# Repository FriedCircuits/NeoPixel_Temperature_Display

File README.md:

NeoPixel Temperature Ring
================

Readme place holder

More info on

http://mobilewill.us

http://www.mobilewill.us/2015/07/arduino-zero-has-arrived.html

License: All source code and designs are released under 

Creative Commons 

CC BY-SA

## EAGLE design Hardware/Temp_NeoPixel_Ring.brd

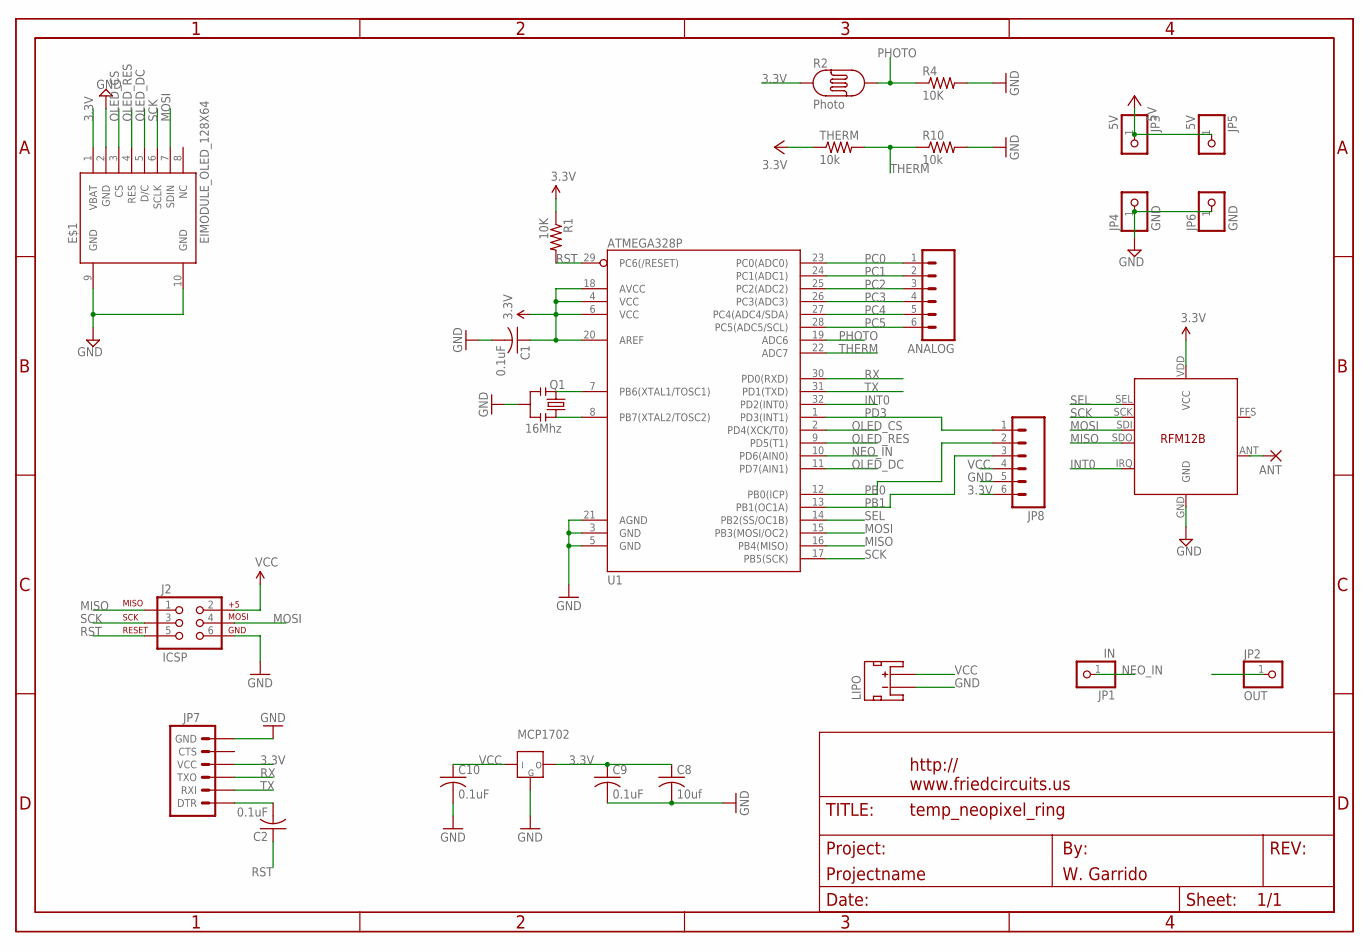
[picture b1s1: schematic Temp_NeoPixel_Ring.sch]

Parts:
ANALOG: M06LOCK; 1X06_LOCK
ANT: 1,6/0,8
C1, C2, C9, C10: 0.1uF; C0805K
C8: 10uf; C0805K
E$1: EIMODULE_OLED_128X64
J2: ICSP; 2X3_LOCK
JP1: IN; 1X01-CLEANBIG
JP2: OUT; 1X01-CLEANBIG
JP3, JP5: 5V; 1X01-CLEANBIG
JP4, JP6: GND; 1X01-CLEANBIG
JP7: ARDUINO_SERIAL_PROGRAMLOCK; 1X06_LOCK
JP8: M06LOCK; 1X06_LOCK
LIPO: LIPO-3.7-6V; JST-2-SMD
MCP1702: MCP1702SOT89; SOT89-3
Q1: 16Mhz; RESONATOR-SMD
R1, R4: 10K; R0805
R2: Photo; PHOTOCELL
R10: 10k; R0805
THERM: 10k; R0805
U1: ATMEGA328P; TQFP32-08
U$1: FRAME_DINA4_L; FC_CREDIT
U$2: RFM12B

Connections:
3.3V: C1.1, C8.1, C9.1, E$1.1 (VBAT), J2.2, JP7.4 (VCC), JP8.6, MCP1702.3 (E), R1.1, R2.1, THERM.1, U1.4 (VCC), U1.6 (VCC), U1.18 (AVCC), U1.20 (AREF), U$2.VDD (VCC)
GND: C1.2, C8.2, C9.2, C10.2, E$1.2 (GND), E$1.9 (GND), E$1.10 (GND), J2.6, JP4.1, JP6.1, JP7.6 (GND), JP8.5, LIPO.1 (-), MCP1702.1 (B), Q1.2, R4.2, R10.2, U1.3 (GND), U1.5 (GND), U1.21 (AGND), U$2.GND
INT0: U1.32 (PD2(INT0)), U$2.IRQ
MISO: J2.1, U1.16 (PB4(MISO)), U$2.SDO
MOSI: E$1.7 (SDIN), J2.4, U1.15 (PB3(MOSI/OC2)), U$2.SDI
unnamed: C2.2, JP7.1 (DTR)
unnamed: Q1.1, U1.8 (PB7(XTAL2/TOSC2))
unnamed: Q1.3, U1.7 (PB6(XTAL1/TOSC1))
unnamed: ANT.1, U$2.ANT
NEO_IN: JP1.1, U1.10 (PD6(AIN0))
OLED_CS: E$1.3 (CS), U1.2 (PD4(XCK/T0))
OLED_DC: E$1.5 (D/C), U1.11 (PD7(AIN1))
OLED_RES: E$1.4 (RES), U1.9 (PD5(T1))
OUT: JP2.1
PB0: JP8.2, U1.12 (PB0(ICP))
PB1: JP8.3, U1.13 (PB1(OC1A))
PC0: ANALOG.1, U1.23 (PC0(ADC0))
PC1: ANALOG.2, U1.24 (PC1(ADC1))
PC2: ANALOG.3, U1.25 (PC2(ADC2))
PC3: ANALOG.4, U1.26 (PC3(ADC3))
PC4: ANALOG.5, U1.27 (PC4(ADC4/SDA))
PC5: ANALOG.6, U1.28 (PC5(ADC5/SCL))
PD3: JP8.1, U1.1 (PD3(INT1))
PHOTO: R2.2, R4.1, U1.19 (ADC6)
RST: C2.1, J2.5, R1.2, U1.29 (PC6(/RESET))
RX: JP7.3 (TXO), U1.30 (PD0(RXD))
SCK: E$1.6 (SCLK), J2.3, U1.17 (PB5(SCK)), U$2.SCK
SEL: U1.14 (PB2(SS/OC1B)), U$2.SEL
THERM: R10.1, THERM.2, U1.22 (ADC7)
TX: JP7.2 (RXI), U1.31 (PD1(TXD))
VCC: C10.1, JP3.1, JP5.1, JP8.4, LIPO.2 (+), MCP1702.2 (C)

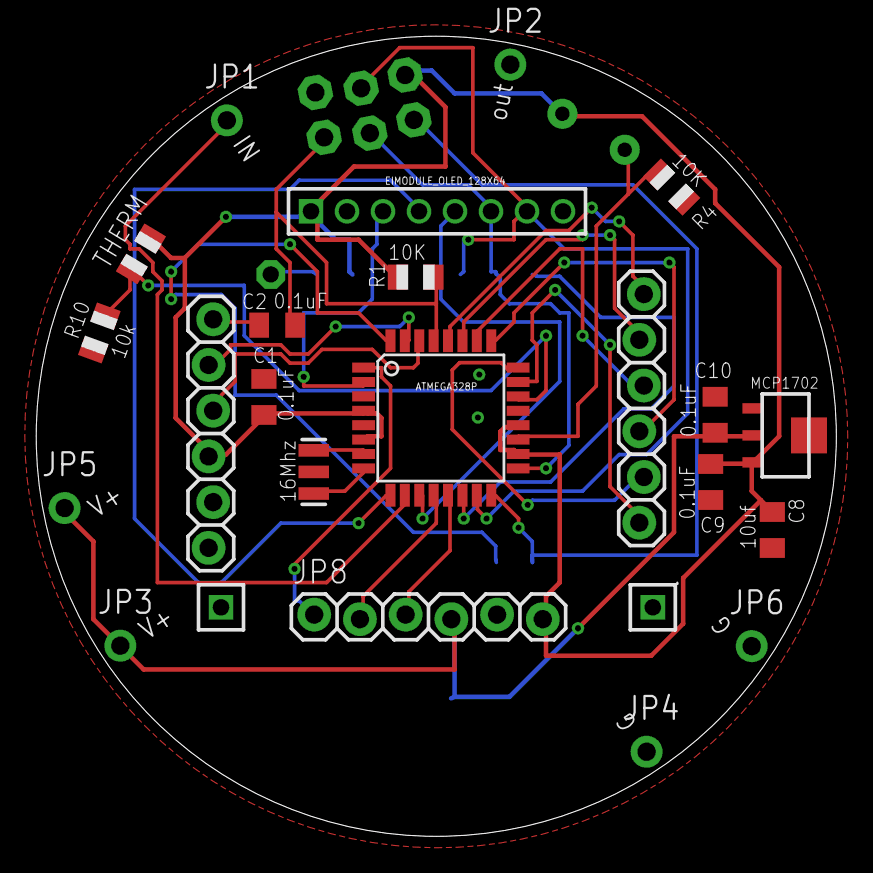
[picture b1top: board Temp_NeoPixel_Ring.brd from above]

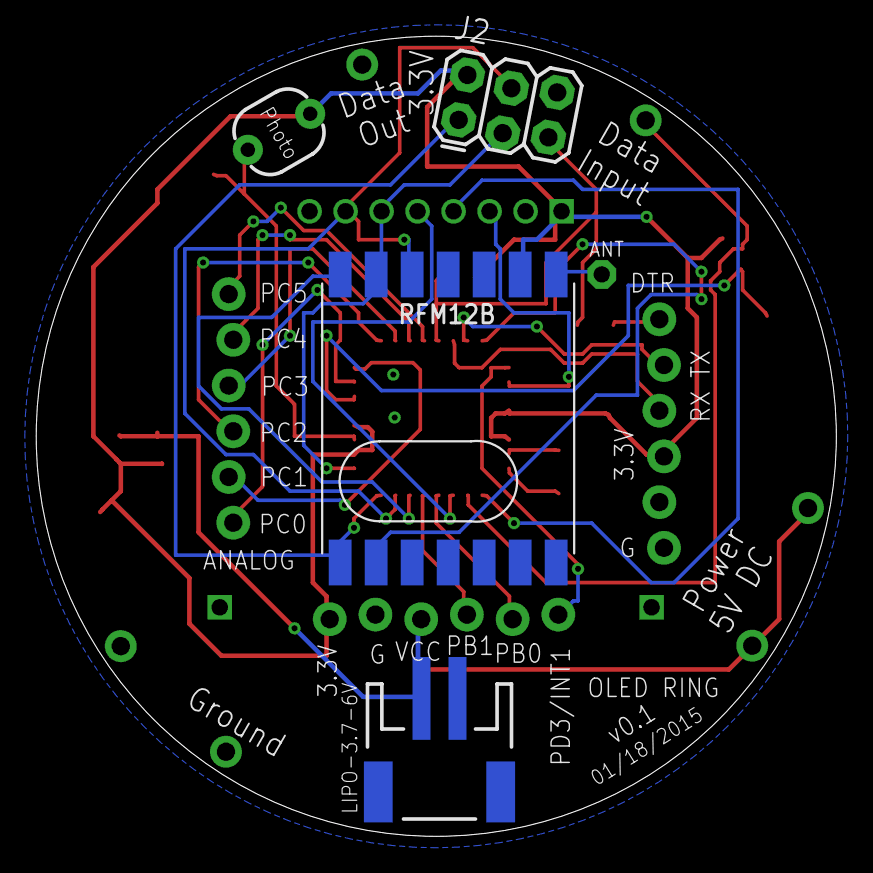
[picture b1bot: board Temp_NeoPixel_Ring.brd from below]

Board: 2 copper layers, 44.5 x 44.5 mm, 28 parts (5 on the bottom side), 30 nets.

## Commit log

2015-07-06 :lollipop: Added .gitattributes

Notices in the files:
parts and their libraries:
microbuilder: This work is placed in the public domain, and may be freely used for commercial and non-commercial work with the following conditions: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
SparkFun-Connectors: Licensing: CC v3.0 Share-Alike You are welcome to use this library for commercial purposes.
